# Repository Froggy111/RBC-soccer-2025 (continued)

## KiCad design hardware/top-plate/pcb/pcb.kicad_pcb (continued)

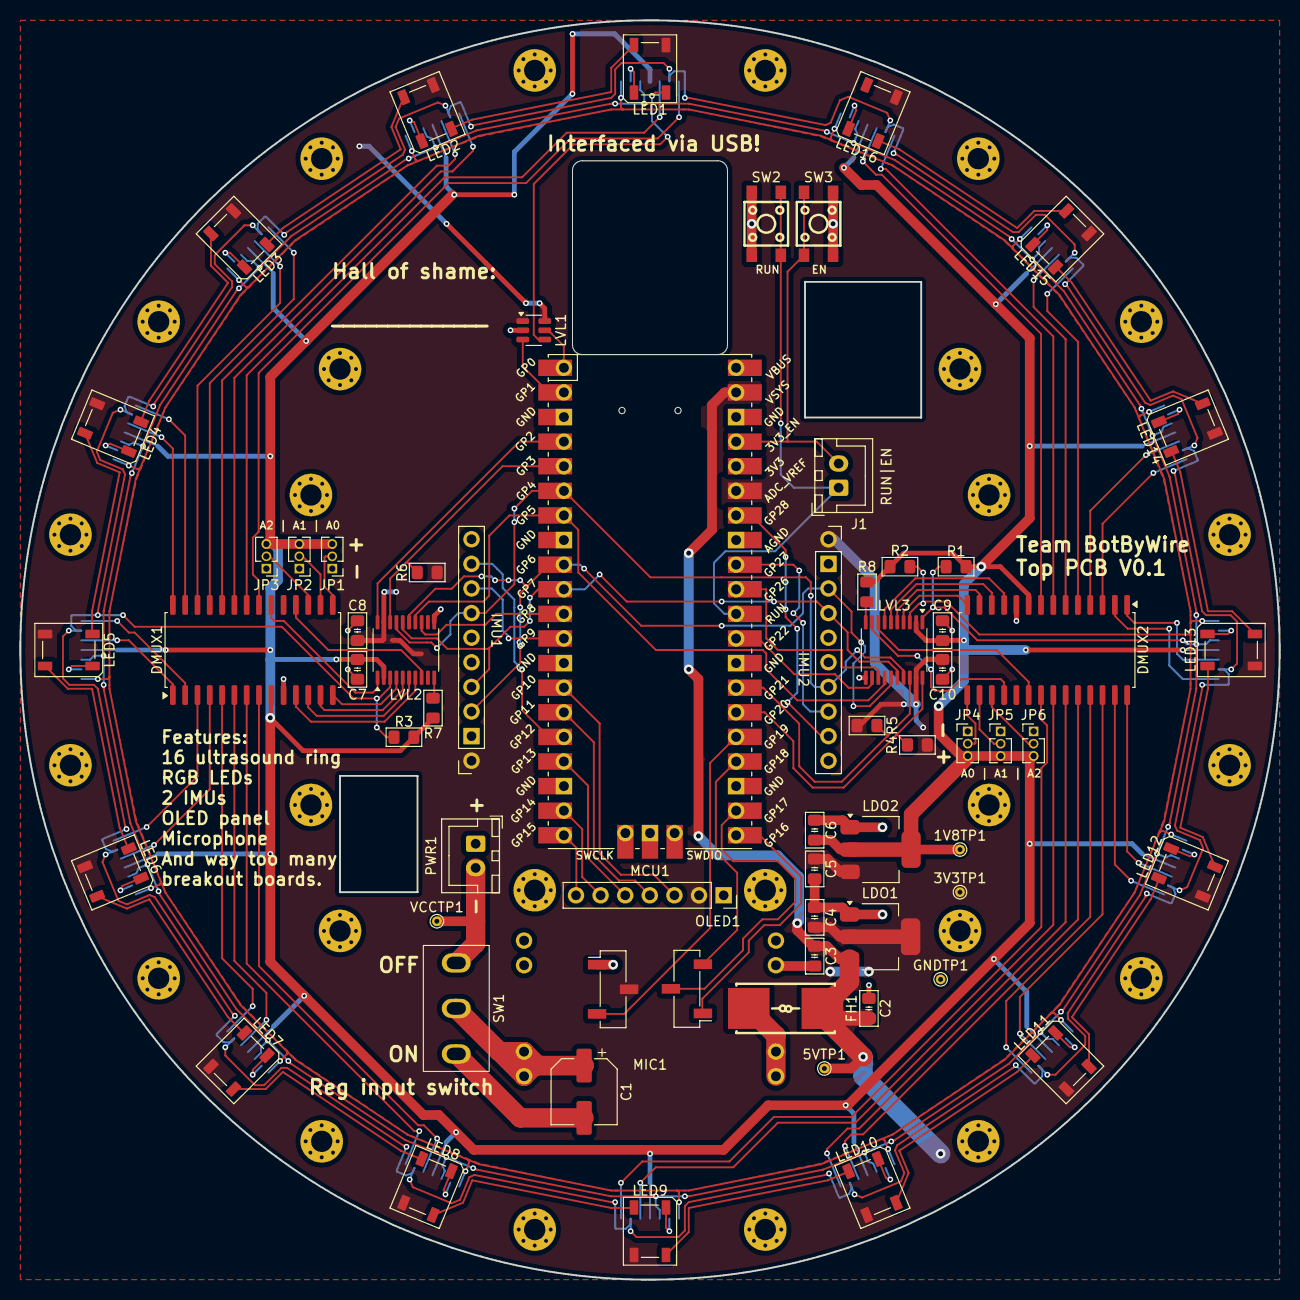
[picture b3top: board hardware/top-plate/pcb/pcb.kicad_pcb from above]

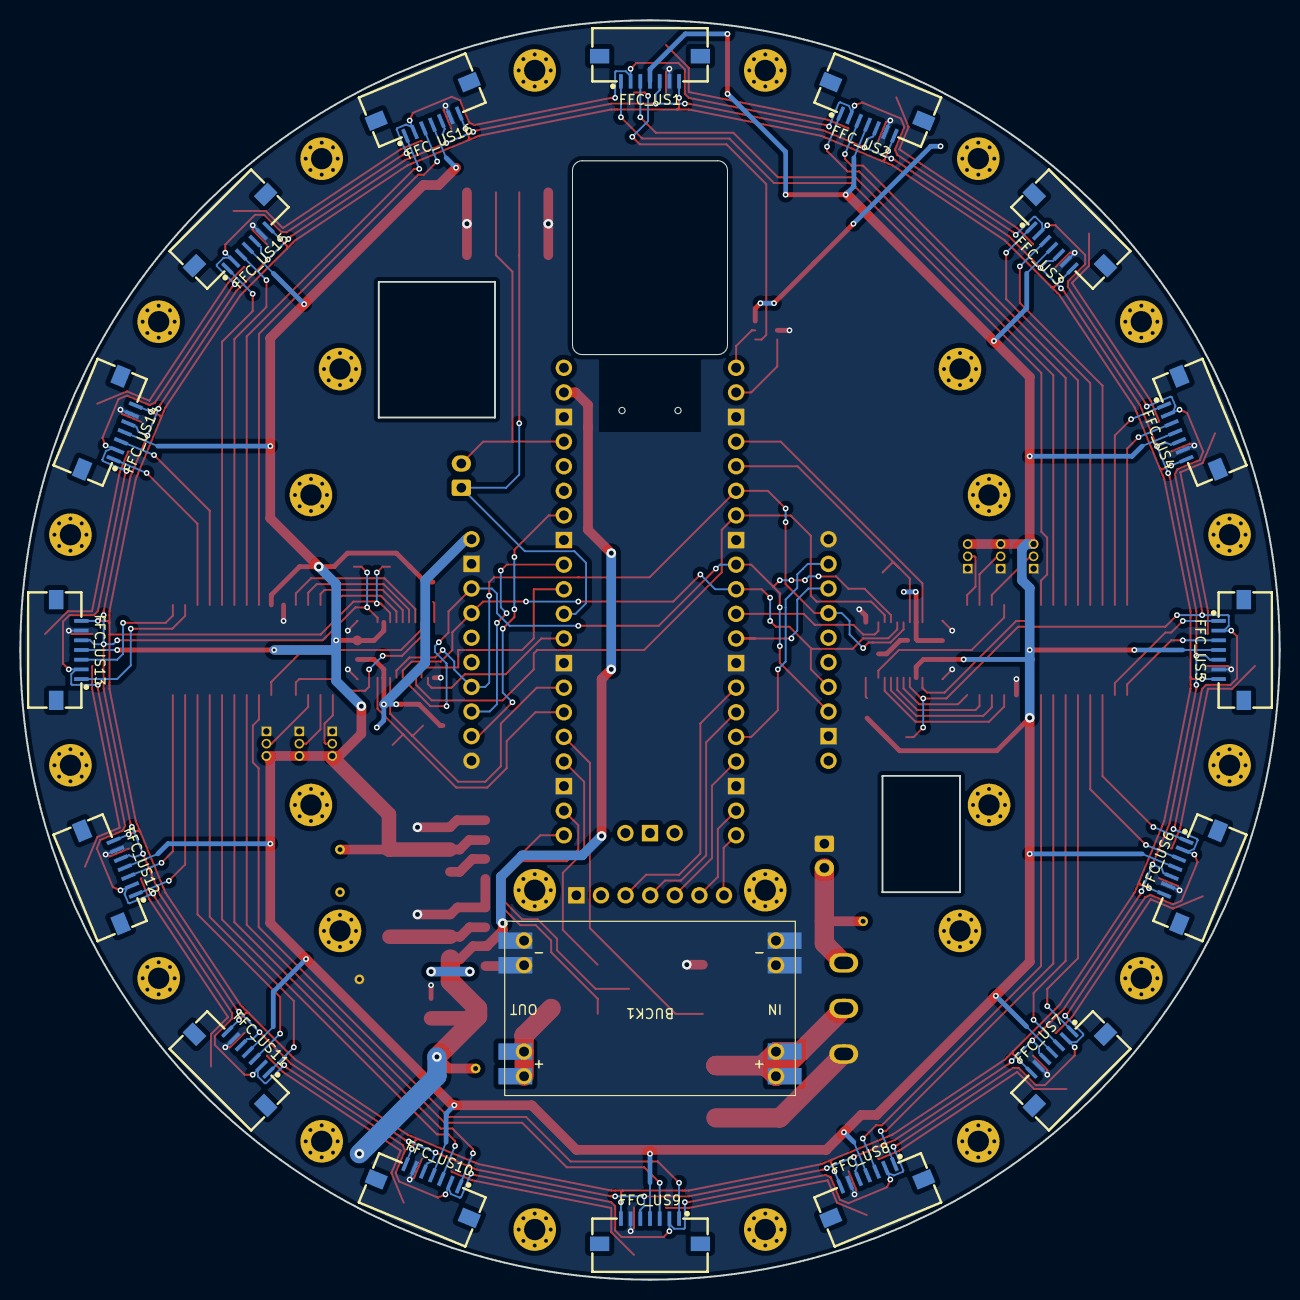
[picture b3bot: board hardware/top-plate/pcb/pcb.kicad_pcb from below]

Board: 2 copper layers, 130.0 x 130.0 mm, 104 parts (17 on the bottom side), 106 nets.

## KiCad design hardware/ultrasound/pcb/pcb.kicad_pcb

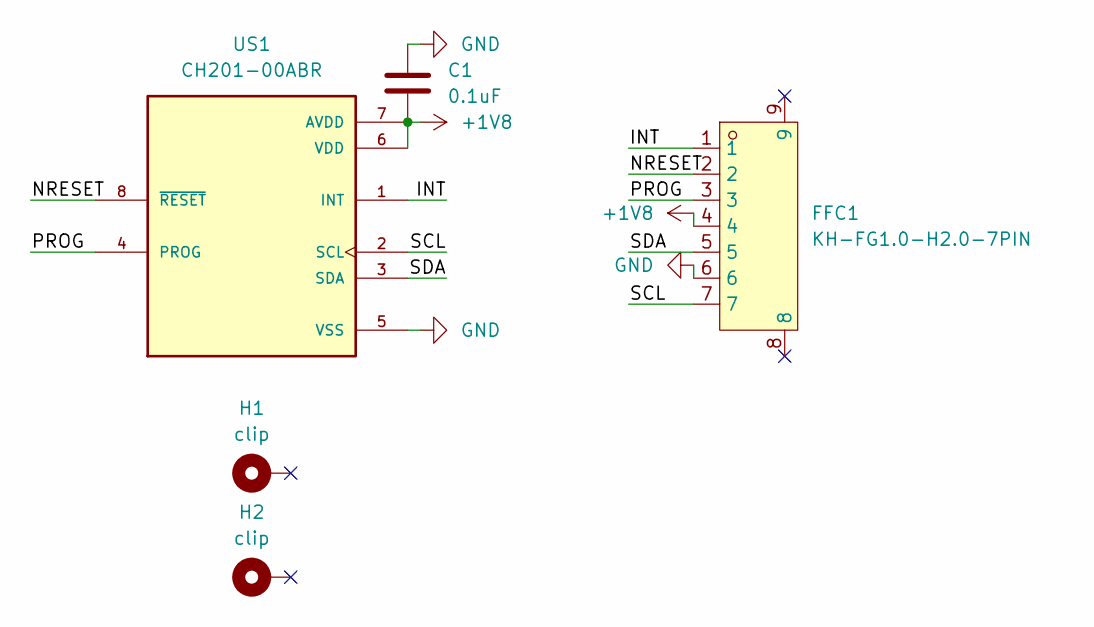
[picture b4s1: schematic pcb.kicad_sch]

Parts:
C1: 0.1uF; C_1206_3216Metric_Pad1.33x1.80mm_HandSolder
FFC1: KH-FG1.0-H2.0-7PIN; FPC-SMD_7P-P1.0_KINGHELM_KH-FG1.0-H2.0-7PIN; LCSC Part C2925379
H1, H2: clip
US1: CH201-00ABR; CH201-00ABR_XDCR_CH201-00ABR; PARTREV 1.1

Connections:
+1V8: C1.2, FFC1.4, US1.6 (VDD), US1.7 (AVDD)
/INT: FFC1.1, US1.1 (INT)
/NRESET: FFC1.2, US1.8 (~RESET)
/PROG: FFC1.3, US1.4 (PROG)
/SCL: FFC1.7, US1.2 (SCL)
/SDA: FFC1.5, US1.3 (SDA)
GND: C1.1, FFC1.6, US1.5 (VSS)

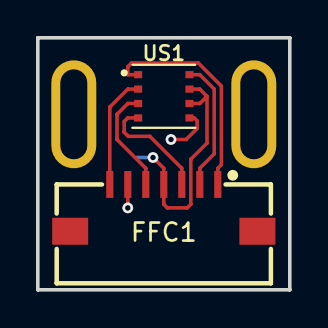
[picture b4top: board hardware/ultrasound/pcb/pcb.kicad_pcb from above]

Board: 2 copper layers, 14.0 x 14.0 mm, 5 parts (1 on the bottom side), 7 nets.

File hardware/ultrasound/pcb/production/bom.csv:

Designator,Footprint,Quantity,Value,LCSC Part #
C1,1206,1,0.1uF,
FFC1,FPC-SMD_7P-P1.0_KINGHELM_KH-FG1.0-H2.0-7PIN,1,KH-FG1.0-H2.0-7PIN,C2925379
US1,CH201-00ABR_XDCR_CH201-00ABR,1,CH201-00ABR,

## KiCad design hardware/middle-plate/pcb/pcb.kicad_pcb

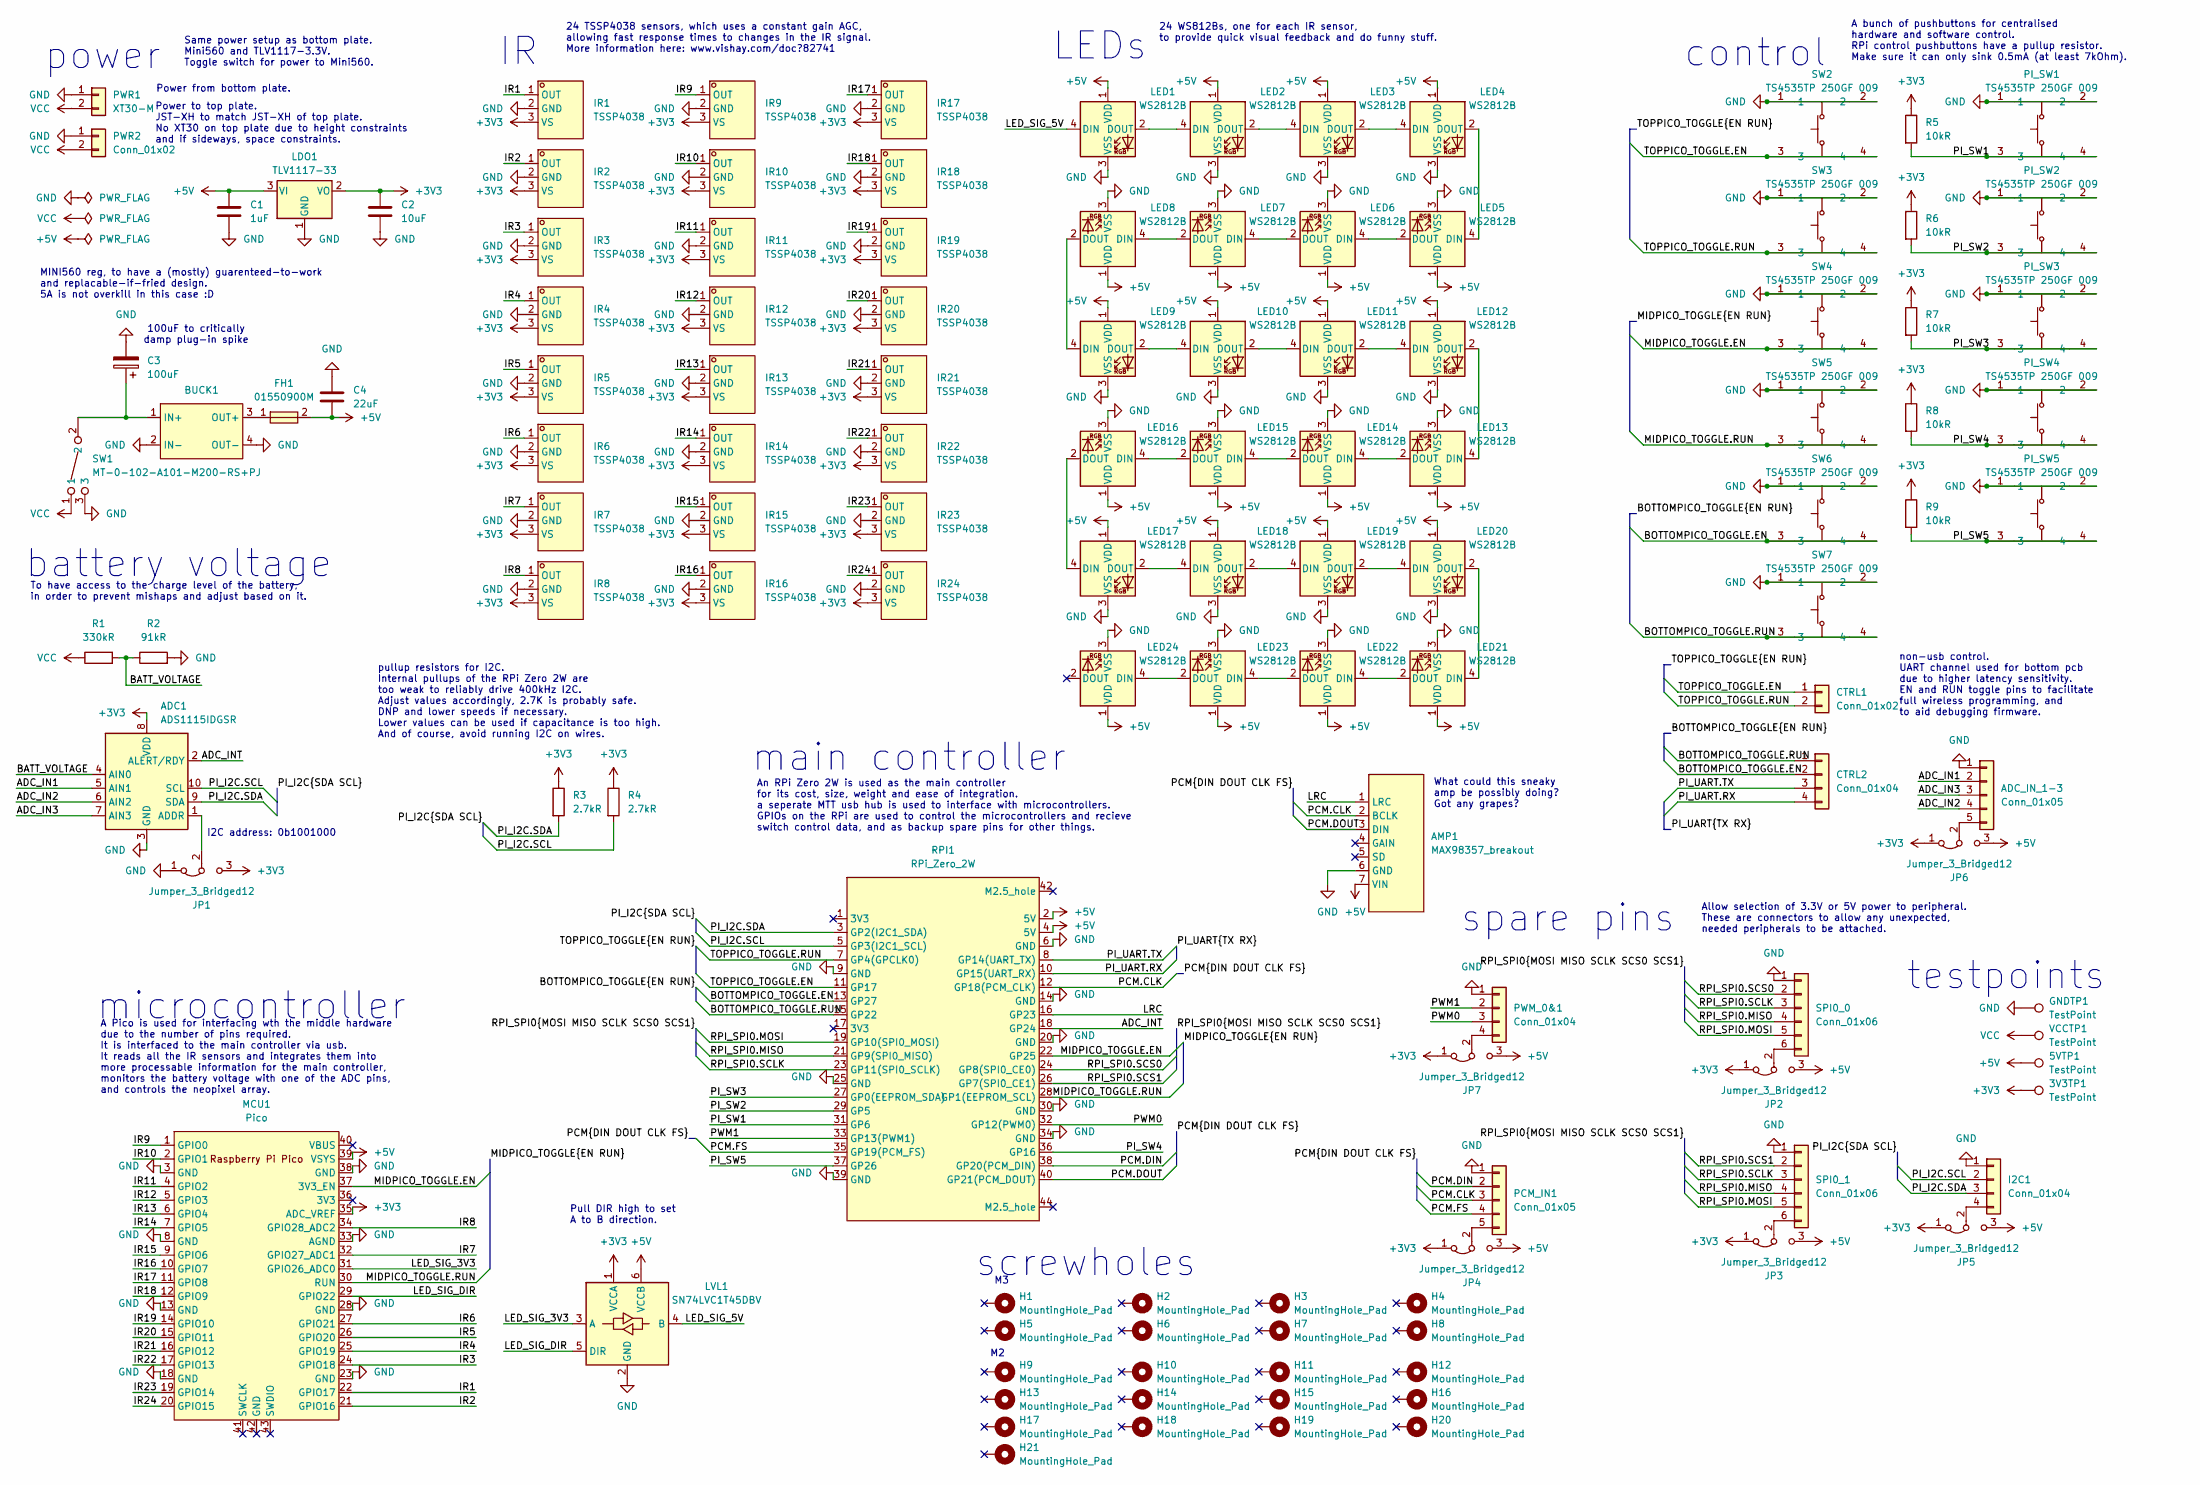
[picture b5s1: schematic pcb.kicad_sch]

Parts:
3V3TP1, 5VTP1: TestPoint; TestPoint_THTPad_D1.0mm_Drill0.5mm
ADC1: ADS1115IDGSR; TSSOP-10_3x3mm_P0.5mm
ADC_IN_1-3: Conn_01x05; JST_XH_B5B-XH-A_1x05_P2.50mm_Vertical
AMP1: MAX98357_breakout; MAX98357_breakout_no_mountingholes
BUCK1: mini560
C1: 1uF; C_0805_2012Metric_Pad1.15x1.40mm_HandSolder
C2: 10uF; C_0805_2012Metric_Pad1.15x1.40mm_HandSolder
C3: 100uF; CP_Elec_6.3x7.7
C4: 22uF; C_0805_2012Metric_Pad1.15x1.40mm_HandSolder
CTRL1: Conn_01x02; JST_XH_B2B-XH-A_1x02_P2.50mm_Vertical
CTRL2: Conn_01x04; JST_XH_B4B-XH-A_1x04_P2.50mm_Vertical
FH1: 01550900M; FUSE-SMD_L9.8-W5.0; LCSC Part C108518
GNDTP1: TestPoint; TestPoint_THTPad_D1.0mm_Drill0.5mm
H1, H2, H3, H4, H5, H6, H7, H8: MountingHole_Pad; MountingHole_3.2mm_M3_Pad_Via
H9, H10, H11, H12, H13, H14, H15, H16, H17, H18, H19, H20, H21: MountingHole_Pad; MountingHole_2.2mm_M2_Pad_Via
I2C1: Conn_01x04; JST_XH_B4B-XH-A_1x04_P2.50mm_Vertical
IR1, IR2, IR3, IR4, IR5, IR6, IR7, IR8, IR9, IR10, IR11, IR12, IR13, IR14, IR15, IR16, IR17, IR18, IR19, IR20, IR21, IR22, IR23, IR24: TSSP4038; SENSOR-TH_TSSP40X; LCSC Part C143753
JP1, JP2, JP3, JP4, JP5, JP6, JP7: Jumper_3_Bridged12; PinHeader_1x03_P1.27mm_Vertical
LDO1: TLV1117-33; SOT-223-3_TabPin2
LED1, LED2, LED3, LED4, LED5, LED6, LED7, LED8, LED9, LED10, LED11, LED12, LED13, LED14, LED15, LED16, LED17, LED18, LED19, LED20, LED21, LED22, LED23, LED24: WS2812B; LED_WS2812B-Mini_PLCC4_3.5x3.5mm
LVL1: SN74LVC1T45DBV; SOT-23-6
MCU1: Pico; RPi_Pico_SMD_TH_USBC_cable_cutout
PCM_IN1: Conn_01x05; JST_XH_B5B-XH-A_1x05_P2.50mm_Vertical
PI_SW1, PI_SW2, PI_SW3, PI_SW4, PI_SW5: TS4535TP 250GF 009; SW-SMD_4P-L4.5-W4.5-P3.00-LS6.8; LCSC Part C5342982
PWM_0&1: Conn_01x04; JST_XH_B4B-XH-A_1x04_P2.50mm_Vertical
PWR1: XT30-M; AMASS_XT30U-M_1x02_P5.0mm_Vertical
PWR2: Conn_01x02; JST_XH_B2B-XH-A_1x02_P2.50mm_Vertical
R1: 330kR; R_1206_3216Metric_Pad1.30x1.75mm_HandSolder
R2: 91kR; R_1206_3216Metric_Pad1.30x1.75mm_HandSolder
R3, R4: 2.7kR; R_1206_3216Metric_Pad1.30x1.75mm_HandSolder
R5, R6, R7, R8, R9: 10kR; R_1206_3216Metric_Pad1.30x1.75mm_HandSolder
RPI1: RPi_Zero_2W; RPi_Zero_2W_no_front_mountingholes
SPI0_0, SPI0_1: Conn_01x06; JST_XH_B6B-XH-A_1x06_P2.50mm_Vertical
SW1: MT-0-102-A101-M200-RS+PJ; SW-TH_MT-0-103-A101-M200-RS; LCSC Part C1788492
SW2, SW3, SW4, SW5, SW6, SW7: TS4535TP 250GF 009; SW-SMD_4P-L4.5-W4.5-P3.00-LS6.8; LCSC Part C5342982
VCCTP1: TestPoint; TestPoint_THTPad_D1.0mm_Drill0.5mm

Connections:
+3V3: 3V3TP1.1, ADC1.8 (VDD), C2.2, IR1.3 (VS), IR2.3 (VS), IR3.3 (VS), IR4.3 (VS), IR5.3 (VS), IR6.3 (VS), IR7.3 (VS), IR8.3 (VS), IR9.3 (VS), IR10.3 (VS), IR11.3 (VS), IR12.3 (VS), IR13.3 (VS), IR14.3 (VS), IR15.3 (VS), IR16.3 (VS), IR17.3 (VS), IR18.3 (VS), IR19.3 (VS), IR20.3 (VS), IR21.3 (VS), IR22.3 (VS), IR23.3 (VS), IR24.3 (VS), JP1.3 (B), JP2.1 (A), JP3.1 (A), JP4.1 (A), JP5.1 (A), JP6.1 (A), JP7.1 (A), LDO1.2 (VO), LVL1.1 (VCCA), MCU1.35 (ADC_VREF), R3.1, R4.1, R5.1, R6.1, R7.1, R8.1, R9.1
+5V: 5VTP1.1, AMP1.7 (VIN), C1.2, C4.2, FH1.2, JP2.3 (B), JP3.3 (B), JP4.3 (B), JP5.3 (B), JP6.3 (B), JP7.3 (B), LDO1.3 (VI), LED1.1 (VDD), LED2.1 (VDD), LED3.1 (VDD), LED4.1 (VDD), LED5.1 (VDD), LED6.1 (VDD), LED7.1 (VDD), LED8.1 (VDD), LED9.1 (VDD), LED10.1 (VDD), LED11.1 (VDD), LED12.1 (VDD), LED13.1 (VDD), LED14.1 (VDD), LED15.1 (VDD), LED16.1 (VDD), LED17.1 (VDD), LED18.1 (VDD), LED19.1 (VDD), LED20.1 (VDD), LED21.1 (VDD), LED22.1 (VDD), LED23.1 (VDD), LED24.1 (VDD), LVL1.6 (VCCB), MCU1.39 (VSYS), RPI1.2 (5V), RPI1.4 (5V)
/ADC_IN1: ADC1.5 (AIN1), ADC_IN_1-3.2
/ADC_IN2: ADC1.6 (AIN2), ADC_IN_1-3.4
/ADC_IN3: ADC1.7 (AIN3), ADC_IN_1-3.3
/ADC_INT: ADC1.2 (ALERT/RDY), RPI1.18 (GP24)
/BATT_VOLTAGE: ADC1.4 (AIN0), R1.2, R2.1
/BOTTOMPICO_TOGGLE.EN: CTRL2.2, RPI1.13 (GP27), SW6.3, SW6.4
/BOTTOMPICO_TOGGLE.RUN: CTRL2.1, RPI1.15 (GP22), SW7.3, SW7.4
/IR1: IR1.1 (OUT), MCU1.22 (GPIO17)
/IR2: IR2.1 (OUT), MCU1.21 (GPIO16)
/IR3: IR3.1 (OUT), MCU1.24 (GPIO18)
/IR4: IR4.1 (OUT), MCU1.25 (GPIO19)
/IR5: IR5.1 (OUT), MCU1.26 (GPIO20)
/IR6: IR6.1 (OUT), MCU1.27 (GPIO21)
/IR7: IR7.1 (OUT), MCU1.32 (GPIO27_ADC1)
/IR8: IR8.1 (OUT), MCU1.34 (GPIO28_ADC2)
/IR9: IR9.1 (OUT), MCU1.1 (GPIO0)
/IR10: IR10.1 (OUT), MCU1.2 (GPIO1)
/IR11: IR11.1 (OUT), MCU1.4 (GPIO2)
/IR12: IR12.1 (OUT), MCU1.5 (GPIO3)
/IR13: IR13.1 (OUT), MCU1.6 (GPIO4)
/IR14: IR14.1 (OUT), MCU1.7 (GPIO5)
/IR15: IR15.1 (OUT), MCU1.9 (GPIO6)
/IR16: IR16.1 (OUT), MCU1.10 (GPIO7)
/IR17: IR17.1 (OUT), MCU1.11 (GPIO8)
/IR18: IR18.1 (OUT), MCU1.12 (GPIO9)
/IR19: IR19.1 (OUT), MCU1.14 (GPIO10)
/IR20: IR20.1 (OUT), MCU1.15 (GPIO11)
/IR21: IR21.1 (OUT), MCU1.16 (GPIO12)
/IR22: IR22.1 (OUT), MCU1.17 (GPIO13)
/IR23: IR23.1 (OUT), MCU1.19 (GPIO14)
/IR24: IR24.1 (OUT), MCU1.20 (GPIO15)
/LED_SIG_3V3: LVL1.3 (A), MCU1.31 (GPIO26_ADC0)
/LED_SIG_5V: LED1.4 (DIN), LVL1.4 (B)
/LED_SIG_DIR: LVL1.5 (DIR), MCU1.29 (GPIO22)
/LRC: AMP1.1 (LRC), RPI1.16 (GP23)
/MIDPICO_TOGGLE.EN: MCU1.37 (3V3_EN), RPI1.22 (GP25), SW4.3, SW4.4
/MIDPICO_TOGGLE.RUN: MCU1.30 (RUN), RPI1.28 (GP1(EEPROM_SCL)), SW5.3, SW5.4
/PCM.CLK: AMP1.2 (BCLK), PCM_IN1.3, RPI1.12 (GP18(PCM_CLK))
/PCM.DIN: PCM_IN1.2, RPI1.38 (GP20(PCM_DIN))
/PCM.DOUT: AMP1.3 (DIN), RPI1.40 (GP21(PCM_DOUT))
/PCM.FS: PCM_IN1.4, RPI1.35 (GP19(PCM_FS))
/PI_I2C.SCL: ADC1.10 (SCL), I2C1.2, R4.2, RPI1.5 (GP3(I2C1_SCL))
/PI_I2C.SDA: ADC1.9 (SDA), I2C1.3, R3.2, RPI1.3 (GP2(I2C1_SDA))
/PI_SW1: PI_SW1.3, PI_SW1.4, R5.2, RPI1.31 (GP6)
/PI_SW2: PI_SW2.3, PI_SW2.4, R6.2, RPI1.29 (GP5)
/PI_SW3: PI_SW3.3, PI_SW3.4, R7.2, RPI1.27 (GP0(EEPROM_SDA))
/PI_SW4: PI_SW4.3, PI_SW4.4, R8.2, RPI1.36 (GP16)
/PI_SW5: PI_SW5.3, PI_SW5.4, R9.2, RPI1.37 (GP26)
/PI_UART.RX: CTRL2.4, RPI1.10 (GP15(UART_RX))
/PI_UART.TX: CTRL2.3, RPI1.8 (GP14(UART_TX))
/PWM0: PWM_0&1.3, RPI1.32 (GP12(PWM0))
/PWM1: PWM_0&1.2, RPI1.33 (GP13(PWM1))
/RPI_SPI0.MISO: RPI1.21 (GP9(SPI0_MISO)), SPI0_0.4, SPI0_1.4
/RPI_SPI0.MOSI: RPI1.19 (GP10(SPI0_MOSI)), SPI0_0.5, SPI0_1.5
/RPI_SPI0.SCLK: RPI1.23 (GP11(SPI0_SCLK)), SPI0_0.3, SPI0_1.3
/RPI_SPI0.SCS0: RPI1.24 (GP8(SPI0_CE0)), SPI0_0.2
/RPI_SPI0.SCS1: RPI1.26 (GP7(SPI0_CE1)), SPI0_1.2
/TOPPICO_TOGGLE.EN: CTRL1.1, RPI1.11 (GP17), SW2.3, SW2.4
/TOPPICO_TOGGLE.RUN: CTRL1.2, RPI1.7 (GP4(GPCLK0)), SW3.3, SW3.4
GND: ADC1.3 (GND), ADC_IN_1-3.1, AMP1.6 (GND), BUCK1.2 (IN-), BUCK1.4 (OUT-), C1.1, C2.1, C3.2, C4.1, GNDTP1.1, I2C1.1, IR1.2 (GND), IR2.2 (GND), IR3.2 (GND), IR4.2 (GND), IR5.2 (GND), IR6.2 (GND), IR7.2 (GND), IR8.2 (GND), IR9.2 (GND), IR10.2 (GND), IR11.2 (GND), IR12.2 (GND), IR13.2 (GND), IR14.2 (GND), IR15.2 (GND), IR16.2 (GND), IR17.2 (GND), IR18.2 (GND), IR19.2 (GND), IR20.2 (GND), IR21.2 (GND), IR22.2 (GND), IR23.2 (GND), IR24.2 (GND), JP1.1 (A), LDO1.1 (GND), LED1.3 (VSS), LED2.3 (VSS), LED3.3 (VSS), LED4.3 (VSS), LED5.3 (VSS), LED6.3 (VSS), LED7.3 (VSS), LED8.3 (VSS), LED9.3 (VSS), LED10.3 (VSS), LED11.3 (VSS), LED12.3 (VSS), LED13.3 (VSS), LED14.3 (VSS), LED15.3 (VSS), LED16.3 (VSS), LED17.3 (VSS), LED18.3 (VSS), LED19.3 (VSS), LED20.3 (VSS), LED21.3 (VSS), LED22.3 (VSS), LED23.3 (VSS), LED24.3 (VSS), LVL1.2 (GND), MCU1.3 (GND), MCU1.8 (GND), MCU1.13 (GND), MCU1.18 (GND), MCU1.23 (GND), MCU1.28 (GND), MCU1.33 (AGND), MCU1.38 (GND), PCM_IN1.1, PI_SW1.1, PI_SW1.2, PI_SW2.1, PI_SW2.2, PI_SW3.1, PI_SW3.2, PI_SW4.1, PI_SW4.2, PI_SW5.1, PI_SW5.2, PWM_0&1.1, PWR1.1, PWR2.1, R2.2, RPI1.6 (GND), RPI1.9 (GND), RPI1.14 (GND), RPI1.20 (GND), RPI1.25 (GND), RPI1.30 (GND), RPI1.34 (GND), RPI1.39 (GND), SPI0_0.1, SPI0_1.1, SW1.3, SW2.1, SW2.2, SW3.1, SW3.2, SW4.1, SW4.2, SW5.1, SW5.2, SW6.1, SW6.2, SW7.1, SW7.2
unnamed: ADC1.1 (ADDR), JP1.2 (C)
unnamed: ADC_IN_1-3.5, JP6.2 (C)
unnamed: BUCK1.1 (IN+), C3.1, SW1.2
unnamed: BUCK1.3 (OUT+), FH1.1
unnamed: I2C1.4, JP5.2 (C)
unnamed: JP2.2 (C), SPI0_0.6
unnamed: JP3.2 (C), SPI0_1.6
unnamed: JP4.2 (C), PCM_IN1.5
unnamed: JP7.2 (C), PWM_0&1.4
unnamed: LED1.2 (DOUT), LED2.4 (DIN)
unnamed: LED2.2 (DOUT), LED3.4 (DIN)
unnamed: LED3.2 (DOUT), LED4.4 (DIN)
unnamed: LED4.2 (DOUT), LED5.4 (DIN)
unnamed: LED5.2 (DOUT), LED6.4 (DIN)
unnamed: LED6.2 (DOUT), LED7.4 (DIN)
unnamed: LED7.2 (DOUT), LED8.4 (DIN)
unnamed: LED8.2 (DOUT), LED9.4 (DIN)
unnamed: LED9.2 (DOUT), LED10.4 (DIN)
unnamed: LED10.2 (DOUT), LED11.4 (DIN)
unnamed: LED11.2 (DOUT), LED12.4 (DIN)
unnamed: LED12.2 (DOUT), LED13.4 (DIN)
unnamed: LED13.2 (DOUT), LED14.4 (DIN)
unnamed: LED14.2 (DOUT), LED15.4 (DIN)
unnamed: LED15.2 (DOUT), LED16.4 (DIN)
unnamed: LED16.2 (DOUT), LED17.4 (DIN)
unnamed: LED17.2 (DOUT), LED18.4 (DIN)
unnamed: LED18.2 (DOUT), LED19.4 (DIN)
unnamed: LED19.2 (DOUT), LED20.4 (DIN)
unnamed: LED20.2 (DOUT), LED21.4 (DIN)
unnamed: LED21.2 (DOUT), LED22.4 (DIN)
unnamed: LED22.2 (DOUT), LED23.4 (DIN)
unnamed: LED23.2 (DOUT), LED24.4 (DIN)
VCC: PWR1.2, PWR2.2, R1.1, SW1.1, VCCTP1.1

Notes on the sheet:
screwholes
Allow selection of 3.3V or 5V power to peripheral. These are connectors to allow any unexpected, needed peripherals to be attached.
microcontroller
24 WS812Bs, one for each IR sensor, to provide quick visual feedback and do funny stuff.
main controller
24 TSSP4038 sensors, which uses a constant gain AGC, allowing fast response times to changes in the IR signal. More information here: www.vishay.com/doc?82741
power
What could this sneaky amp be possibly doing? Got any grapes?
MINI560 reg, to have a (mostly) guarenteed-to-work and replacable-if-fried design. 5A is not overkill in this case :D
control
I2C address: 0b1001000
LEDs
pullup resistors for I2C. Internal pullups of the RPi Zero 2W are too weak to reliably drive 400kHz I2C. Adjust values accordingly, 2.7K is probably safe. DNP and lower speeds if necessary. Lower values can be used if capacitance is too high. And of course, avoid running I2C on wires.
Power from bottom plate.
spare pins
A bunch of pushbuttons for centralised hardware and software control. RPi control pushbuttons have a pullup resistor. Make sure it can only sink 0.5mA (at least 7kOhm).
A Pico is used for interfacing wth the middle hardware due to the number of pins required. It is interfaced to the main controller via usb. It reads all the IR sensors and integrates them into more processable information for the main controller, monitors the battery voltage with one of the ADC pin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
An RPi Zero 2W is used as the main controller for its cost, size, weight and ease of integration. a seperate MTT usb hub is used to interface with microcontrollers. GPIOs on the RPi are used to control the microcontrollers and recieve switch control data, and as backup spare pins for other things.
To have access to the charge level of the battery, in order to prevent mishaps and adjust based on it.
testpoints
Power to top plate. JST-XH to match JST-XH of top plate. No XT30 on top plate due to height constraints and if sideways, space constraints.
Pull DIR high to set A to B direction.
100uF to critically damp plug-in spike
battery voltage
Same power setup as bottom plate. Mini560 and TLV1117-3.3V. Toggle switch for power to Mini560.
non-usb control. UART channel used for bottom pcb due to higher latency sensitivity. EN and RUN toggle pins to facilitate full wireless programming, and to aid debugging firmware.

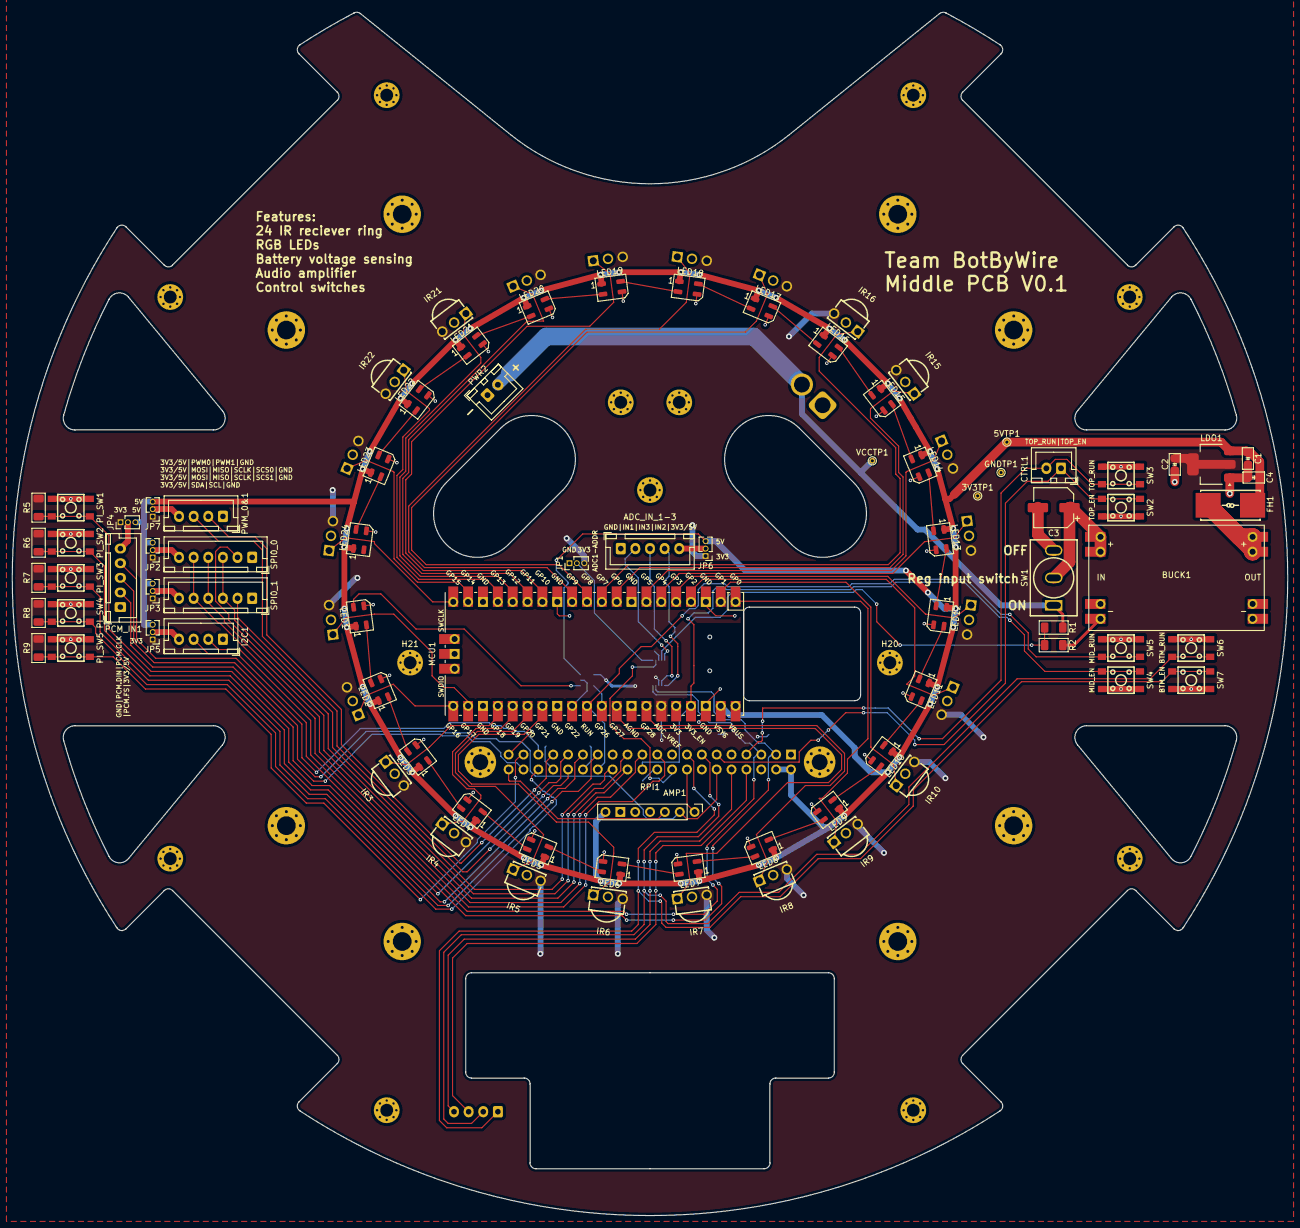
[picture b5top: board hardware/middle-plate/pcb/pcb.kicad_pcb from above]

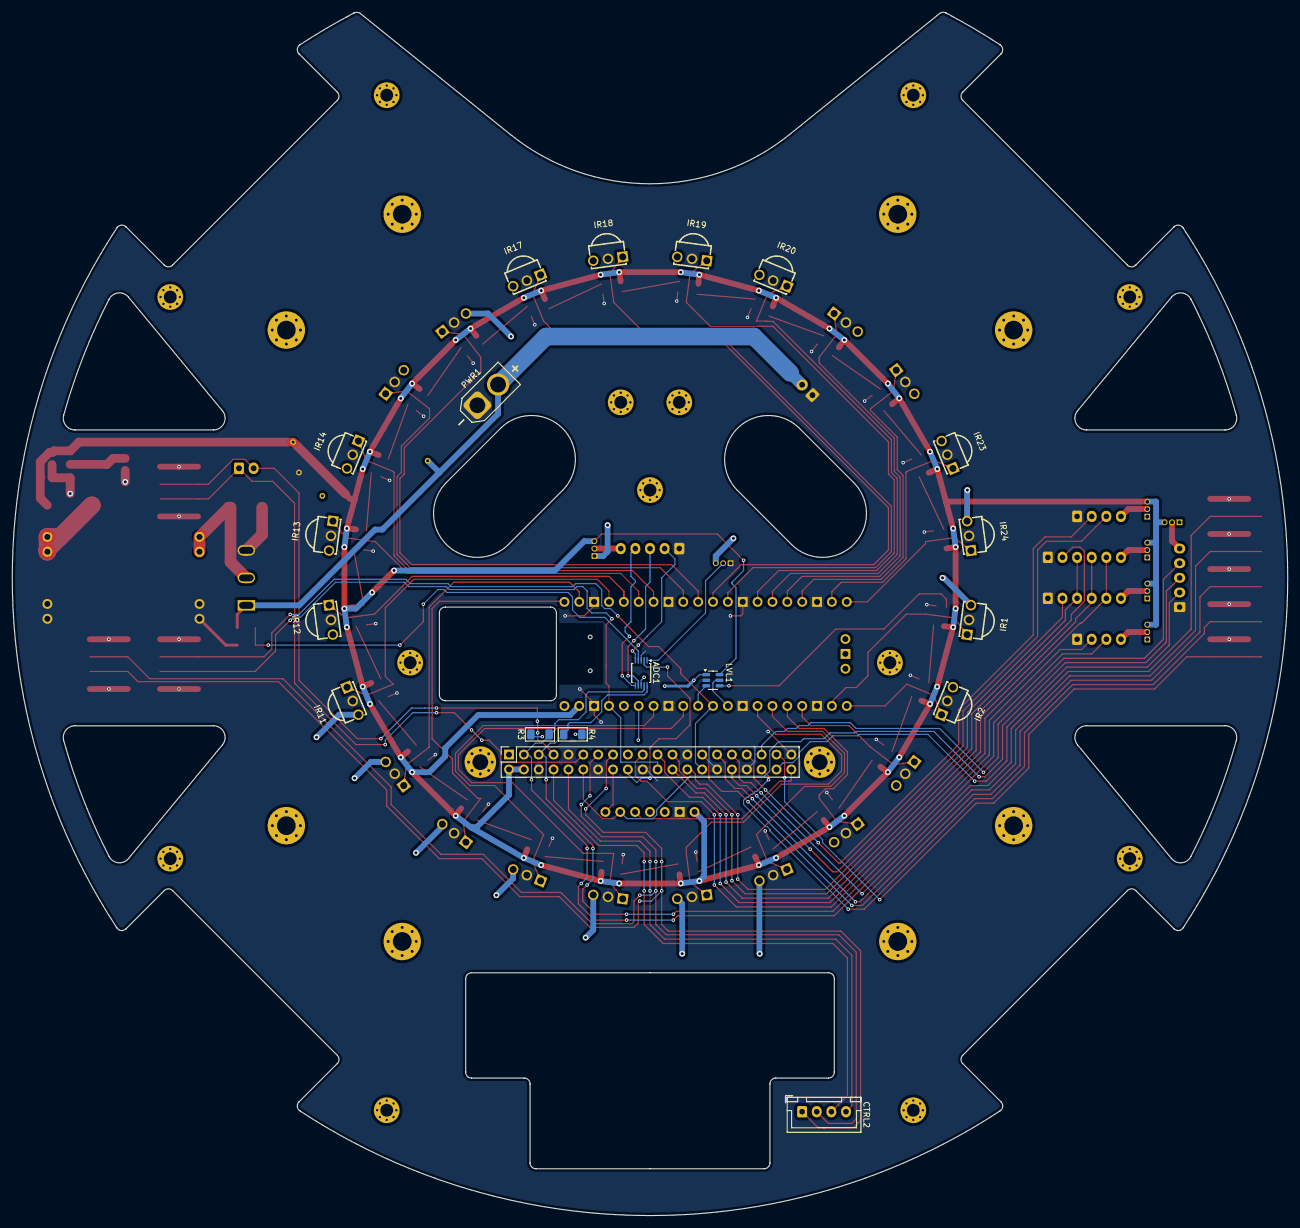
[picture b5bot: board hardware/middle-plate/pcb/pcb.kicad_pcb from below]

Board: 2 copper layers, 218.0 x 205.7 mm, 123 parts (18 on the bottom side), 95 nets.

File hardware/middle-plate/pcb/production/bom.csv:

Designator,Footprint,Quantity,Value,LCSC Part #
"3V3TP1, 5VTP1, GNDTP1, VCCTP1",TestPoint_THTPad_D1.0mm_Drill0.5mm,4,TestPoint,
ADC1,TSSOP-10_3x3mm_P0.5mm,1,ADS1115IDGSR,
"ADC_IN_1-3, PCM_IN1",JST_XH_B5B-XH-A_1x05_P2.50mm_Vertical,2,Conn_01x05,
AMP1,MAX98357_breakout_no_mountingholes,1,MAX98357_breakout,
BUCK1,mini560,1,~,
C1,0805,1,1uF,
C2,0805,1,10uF,
C3,CP_Elec_6.3x7.7,1,100uF,
C4,0805,1,22uF,
"CTRL1, PWR2",JST_XH_B2B-XH-A_1x02_P2.50mm_Vertical,2,Conn_01x02,
"CTRL2, I2C1, PWM_0&1",JST_XH_B4B-XH-A_1x04_P2.50mm_Vertical,3,Conn_01x04,
FH1,FUSE-SMD_L9.8-W5.0,1,01550900M,C108518
"IR1, IR10, IR11, IR12, IR13, IR14, IR15, IR16, IR17, IR18, IR19, IR2, IR20, IR21, IR22, IR23, IR24, IR3, IR4, IR5, IR6, IR7, IR8, IR9",SENSOR-TH_TSSP40X,24,TSSP4038,C143753
LDO1,SOT-223-3_TabPin2,1,TLV1117-33,
"LED1, LED10, LED11, LED12, LED13, LED14, LED15, LED16, LED17, LED18, LED19, LED2, LED20, LED21, LED22, LED23, LED24, LED3, LED4, LED5, LED6, LED7, LED8, LED9",LED_WS2812B-Mini_PLCC4_3.5x3.5mm,24,WS2812B,
LVL1,SOT-23-6,1,SN74LVC1T45DBV,
MCU1,RPi_Pico_SMD_TH_USBC_cable_cutout,1,Pico,
"PI_SW1, PI_SW2, PI_SW3, PI_SW4, PI_SW5, SW2, SW3, SW4, SW5, SW6, SW7",SW-SMD_4P-L4.5-W4.5-P3.00-LS6.8,11,TS4535TP 250GF 009,C5342982
PWR1,AMASS_XT30U-M_1x02_P5.0mm_Vertical,1,XT30-M,
R1,1206,1,330kR,
R2,1206,1,91kR,
"R3, R4",1206,2,2.7kR,
"R5, R6, R7, R8, R9",1206,5,10kR,
RPI1,RPi_Zero_2W_no_front_mountingholes,1,RPi_Zero_2W,
"SPI0_0, SPI0_1",JST_XH_B6B-XH-A_1x06_P2.50mm_Vertical,2,Conn_01x06,
SW1,SW-TH_MT-0-103-A101-M200-RS,1,MT-0-102-A101-M200-RS+PJ,C1788492
